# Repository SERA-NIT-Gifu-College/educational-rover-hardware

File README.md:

# educational-rover-hardware

教育用ローバーのハードウェア仕様

オンボードコンピューターにRaspberry Pi Zero/Wを使用した教育用ローバーの設計書です。

## ピン配置

### DRV8835 (Motor Driver)

| Part/Leg | Raspberry Pi GPIO |
| --- | --- |
| AIN1 | 18 |
| AIN2 | 23 |
| BIN1 | 24 |
| BIN2 | 25 |

### SSD1306 (OLED Display)

| Part/Leg | Raspberry Pi GPIO |
| --- | --- |
| SDA | 2 |
| SCL | 3 |
| VCC | 1 |
| GND | (GND) |

### BMX055 (9 Axes Sensor)

| Part/Leg | Raspberry Pi GPIO |
| --- | --- |
| SDA | 2 |
| SCL | 3 |
| VCC | 1 |
| VCCIO | X |
| 3V3 | 1 |
| GND | (GND) |

### LEDs

| Part/Leg | Raspberry Pi GPIO |
| --- | --- |
| LED1 | 16 |
| LED2 | 20 |
| LED3 | 21 |

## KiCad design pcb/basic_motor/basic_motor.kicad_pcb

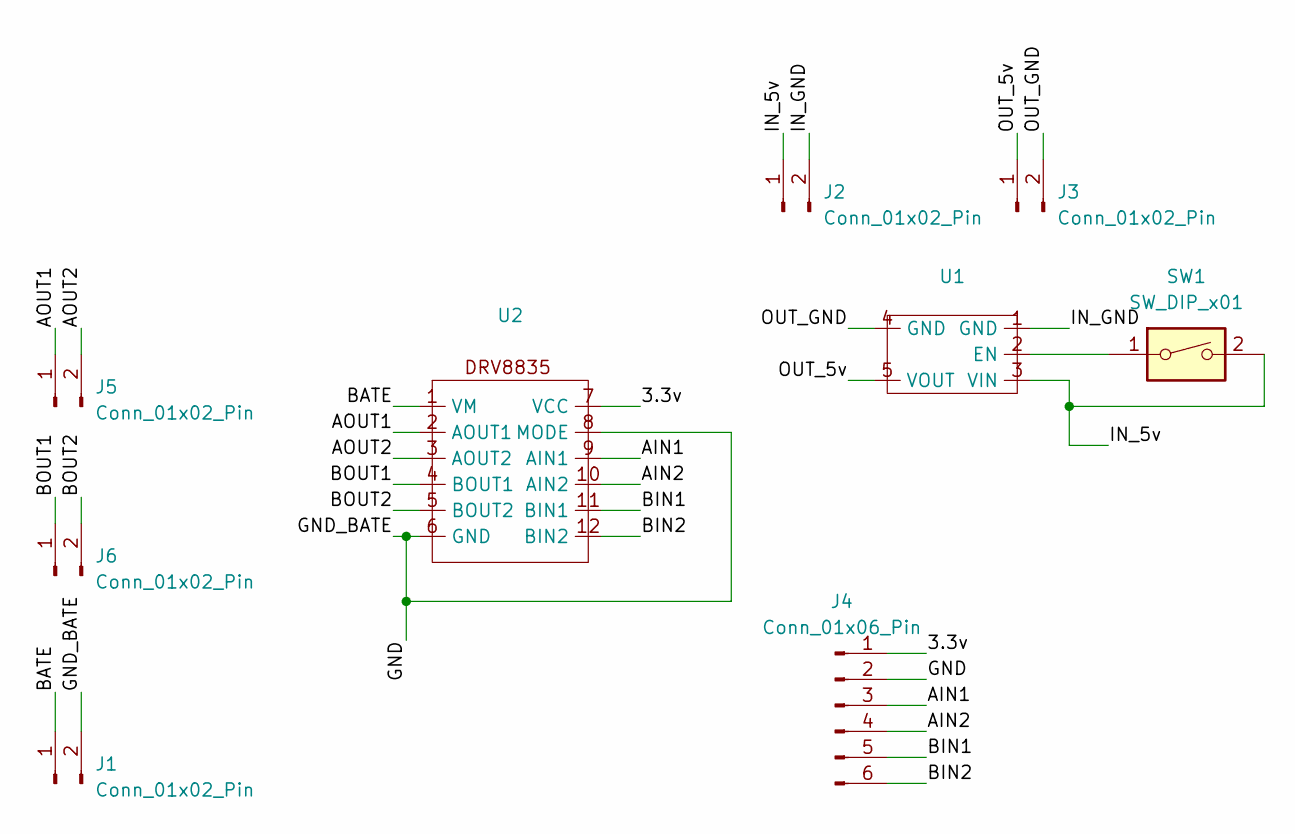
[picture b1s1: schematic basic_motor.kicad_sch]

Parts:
J1, J2: Conn_01x02_Pin; JST_PH_S2B-PH-K_1x02_P2.00mm_Horizontal
J3: Conn_01x02_Pin; PinHeader_1x02_P2.54mm_Horizontal
J4: Conn_01x06_Pin; PinHeader_1x06_P2.54mm_Horizontal
J5, J6: Conn_01x02_Pin; PinHeader_1x02_P2.54mm_Vertical
SW1: SW_DIP_x01; SWITCH
U1: TPS61230A
U2: DRV8835

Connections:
/3.3v: J4.1, U2.7 (VCC)
/AIN1: J4.3, U2.9 (AIN1)
/AIN2: J4.4, U2.10 (AIN2)
/AOUT1: J5.1, U2.2 (AOUT1)
/AOUT2: J5.2, U2.3 (AOUT2)
/BATE: J1.1, U2.1 (VM)
/BIN1: J4.5, U2.11 (BIN1)
/BIN2: J4.6, U2.12 (BIN2)
/BOUT1: J6.1, U2.4 (BOUT1)
/BOUT2: J6.2, U2.5 (BOUT2)
/GND: J1.2, J4.2, U2.6 (GND), U2.8 (MODE)
/IN_5v: J2.1, SW1.2, U1.3 (VIN)
/IN_GND: J2.2, U1.1 (GND)
/OUT_5v: J3.1, U1.5 (VOUT)
/OUT_GND: J3.2, U1.4 (GND)
unnamed: SW1.1, U1.2 (EN)

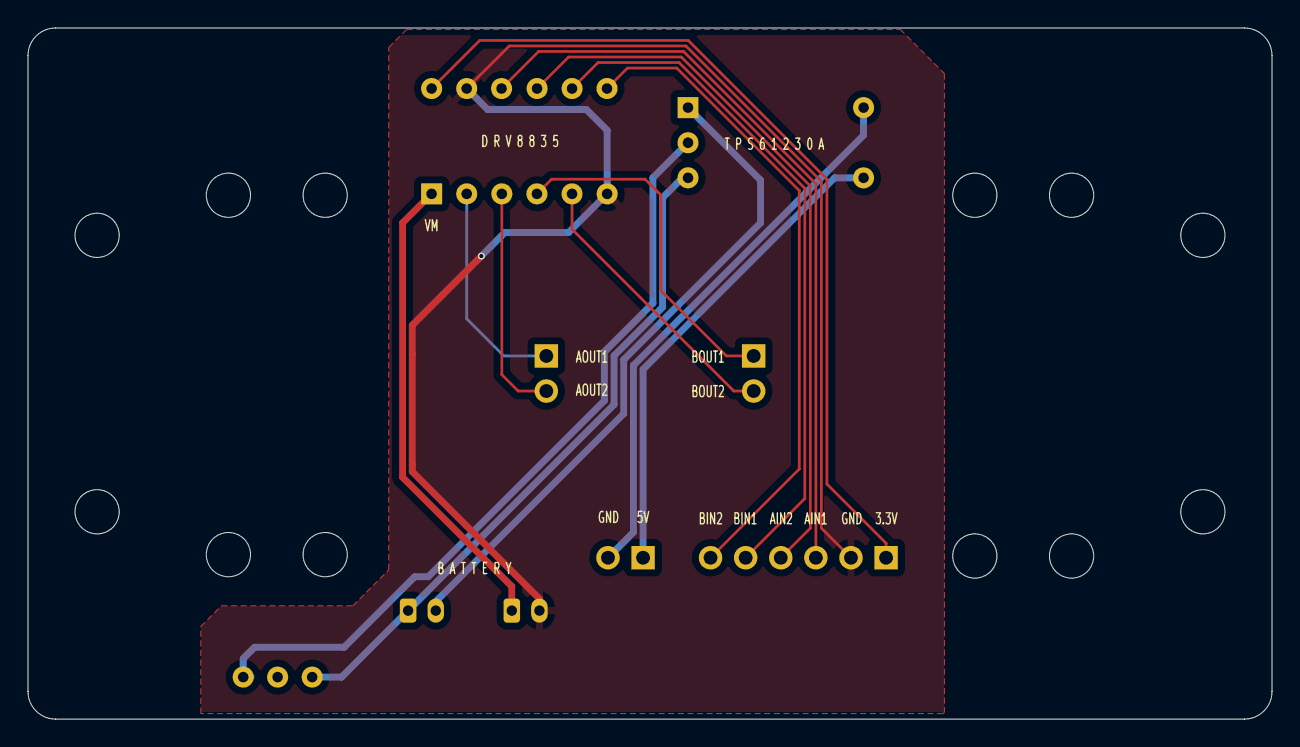
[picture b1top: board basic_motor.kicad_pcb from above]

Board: 2 copper layers, 90.0 x 50.0 mm, 9 parts (0 on the bottom side), 16 nets.

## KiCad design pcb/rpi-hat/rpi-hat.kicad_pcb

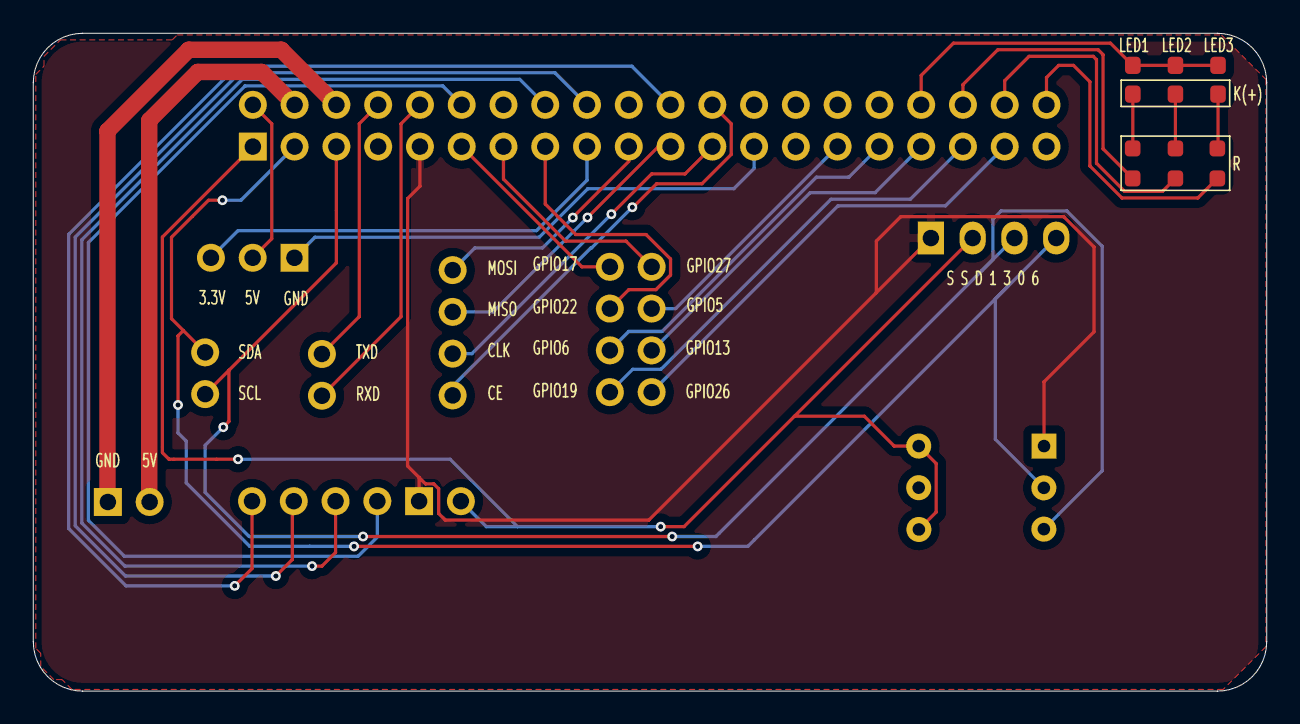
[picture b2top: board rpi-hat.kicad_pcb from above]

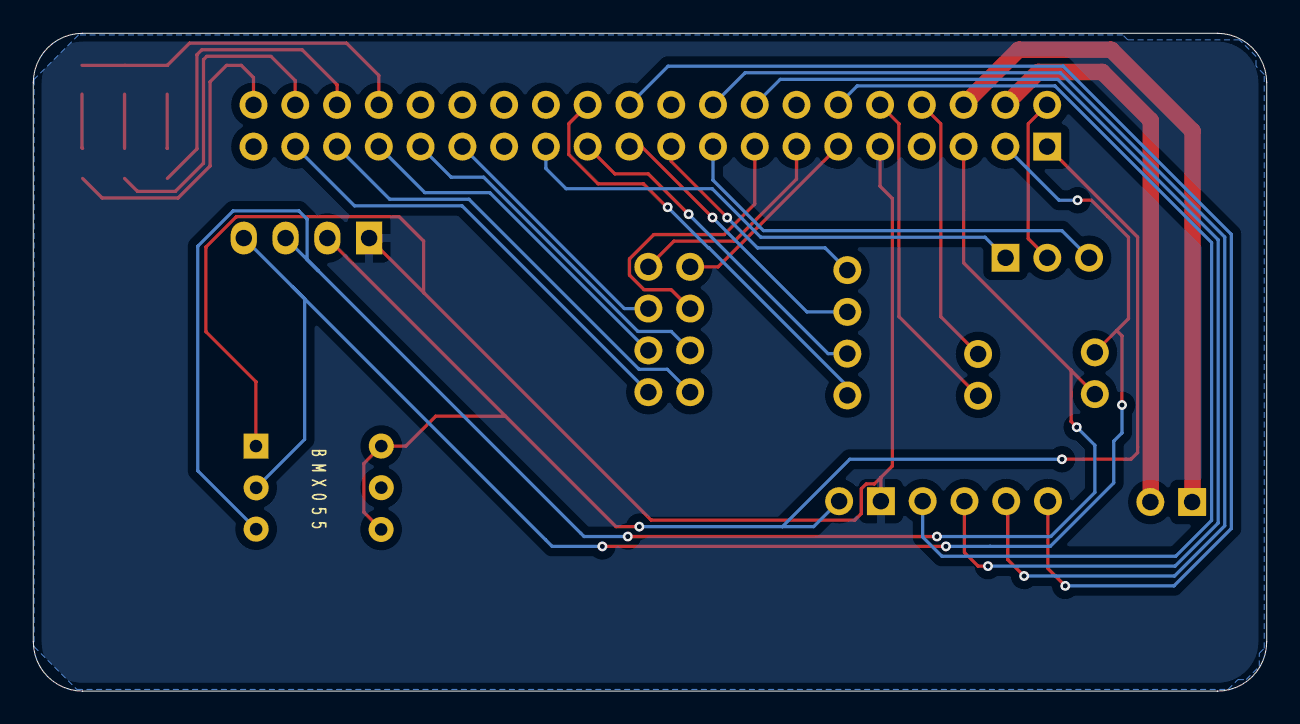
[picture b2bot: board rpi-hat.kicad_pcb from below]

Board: 2 copper layers, 75.0 x 40.0 mm, 16 parts (4 on the bottom side), 34 nets.

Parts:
BMX055: BMX055
Brd1: SSD1306; 128x64OLED
D1, D2, D3: LED; LED_0603_1608Metric_Pad1.05x0.95mm_HandSolder
J1, J3, J4: Conn_01x02_Pin; PinHeader_1x02_P2.54mm_Vertical
J2: Conn_01x06_Pin; PinHeader_1x06_P2.54mm_Vertical
J5: Conn_01x03_Pin; PinHeader_1x03_P2.54mm_Vertical
J6: Conn_01x04_Pin; PinHeader_1x04_P2.54mm_Vertical
J7: Conn_01x08_Pin; PinHeader_2x04_P2.54mm_Vertical
R1, R2, R3: R; R_0603_1608Metric_Pad0.98x0.95mm_HandSolder
u1: PinSocket_2x20_P2.54mm_Vertical

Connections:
/3.3V_OUT: J5.1, u1.17 (3.3v)
/5V_OUT: J5.2, u1.2 (5v)
/5v_IN: J1.1, u1.4 (5v)
/AIN1: J2.4, u1.12 (GPIO18)
/AIN2: J2.3, u1.16 (GPIO23)
/BIN1: J2.2, u1.18 (GPIO24)
/BIN2: J2.1, u1.22 (GPIO25)
/CE: J6.4, u1.24 (GPIO8(CE0))
/CLK: J6.3, u1.23 (GPIO11(CLK))
/GND: Brd1.1 (GND), J2.5, u1.9 (GND)
/GND_IN: J1.2, u1.6 (GND)
/GND_LED: D1.2 (A), D2.2 (A), D3.2 (A), u1.34 (GND)
/GND_OUT: J5.3, u1.25 (GND)
/GP5: J7.4, u1.29 (GPIO5)
/GP6: J7.5, u1.31 (GPIO6)
/GP13: J7.6, u1.33 (GPIO13)
/GP17: J7.1, u1.11 (GPIO17)
/GP19: J7.7, u1.35 (GPIO19)
/GP22: J7.3, u1.15 (GPIO22)
/GP26: J7.8, u1.37 (GPIO26)
/GP27: J7.2, u1.13 (GPIO27)
/LED1: R1.2, u1.36 (GPIO16)
/LED2: R2.2, u1.38 (GPIO20)
/LED3: R3.2, u1.40 (GPIO21)
/MISO: J6.2, u1.21 (GPIO9(MISO))
/MOSI: J6.1, u1.19 (GPIO10(MOSI))
/RXD: J4.2, u1.10 (GPIO15(RXD))
/SCL: Brd1.3 (SCL), J3.2, u1.5 (GPIO3(SCL))
/SDA: Brd1.4 (SDA), J3.1, u1.3 (GPIO2(SDA))
/TXD: J4.1, u1.8 (GPIO14(TXD))
/VCC: Brd1.2 (VCC), J2.6, u1.1 (3.3v)
unnamed: D1.1 (K), R1.1
unnamed: D2.1 (K), R2.1
unnamed: D3.1 (K), R3.1

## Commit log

2024-12-12 Create LICENSE
2024-12-12 Added PCBs
2024-12-26 Added 3D models, added parts on list
